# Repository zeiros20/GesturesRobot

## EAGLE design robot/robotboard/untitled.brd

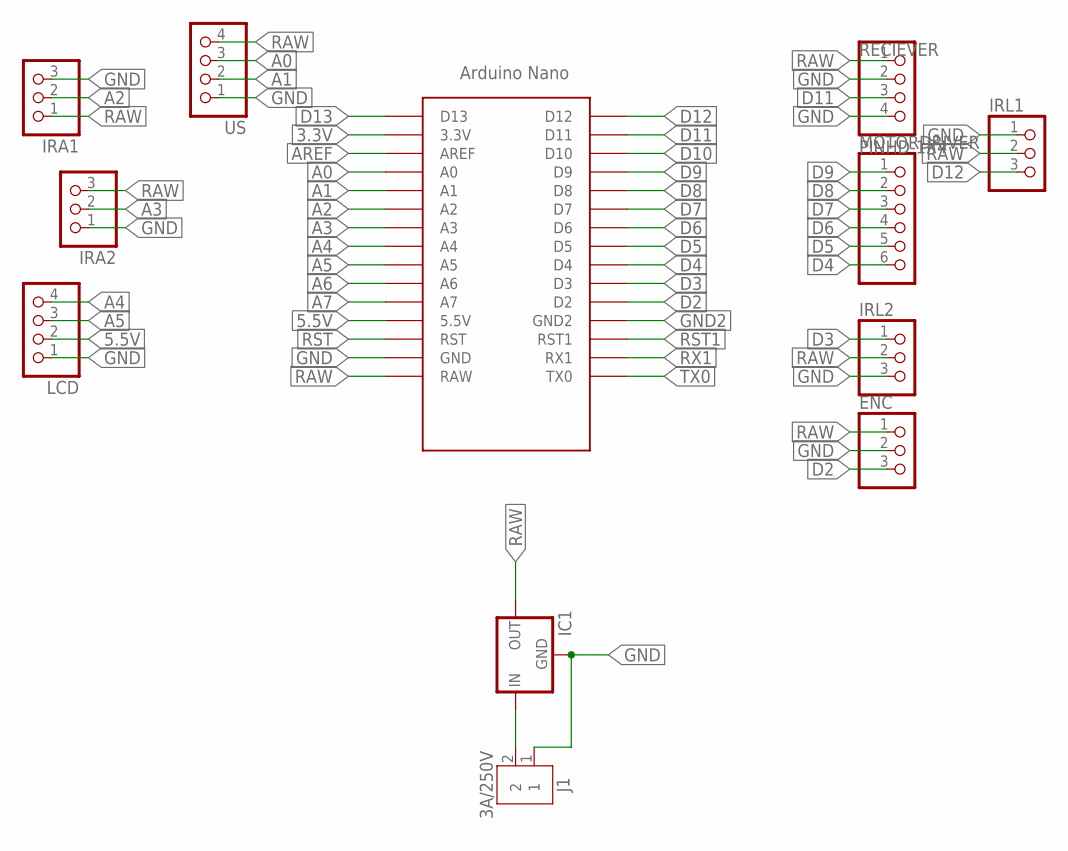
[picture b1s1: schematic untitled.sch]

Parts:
ENC: PINHD-1X3; 1X03
IC1: 78XXS
IRA1, IRA2: PINHD-1X3; 1X03
IRL1, IRL2: PINHD-1X3; 1X03
J1: 3A/250V; B2B-XH-A
LCD: PINHD-1X4; 1X04
MOTORDRIVER: PINHD-1X6; 1X06
RECIEVER: PINHD-1X4; 1X04
U$1: ARDUINO_NANO; NANO
US: PINHD-1X4; 1X04

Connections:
3.3V: U$1.3.3V
5.5V: LCD.2, U$1.5V (5.5V)
A0: U$1.A0, US.3
A1: U$1.A1, US.2
A2: IRA1.2, U$1.A2
A3: IRA2.2, U$1.A3
A4: LCD.4, U$1.A4
A5: LCD.3, U$1.A5
A6: U$1.A6
A7: U$1.A7
AREF: U$1.AREF
D2: ENC.3, U$1.D2
D3: IRL2.1, U$1.D3
D4: MOTORDRIVER.6, U$1.D4
D5: MOTORDRIVER.5, U$1.D5
D6: MOTORDRIVER.4, U$1.D6
D7: MOTORDRIVER.3, U$1.D7
D8: MOTORDRIVER.2, U$1.D8
D9: MOTORDRIVER.1, U$1.D9
D10: U$1.D10
D11: RECIEVER.3, U$1.D11
D12: IRL1.3, U$1.D12
D13: U$1.D13
GND: ENC.2, IC1.GND, IRA1.3, IRA2.1, IRL1.1, IRL2.3, J1.1, LCD.1, RECIEVER.2, RECIEVER.4, U$1.GND, US.1
GND2: U$1.GND1 (GND2)
unnamed: IC1.IN, J1.2
RAW: ENC.1, IC1.OUT, IRA1.1, IRA2.3, IRL1.2, IRL2.2, RECIEVER.1, U$1.RAW, US.4
RST: U$1.RST
RST1: U$1.RST1
RX1: U$1.RX1
TX0: U$1.TX0

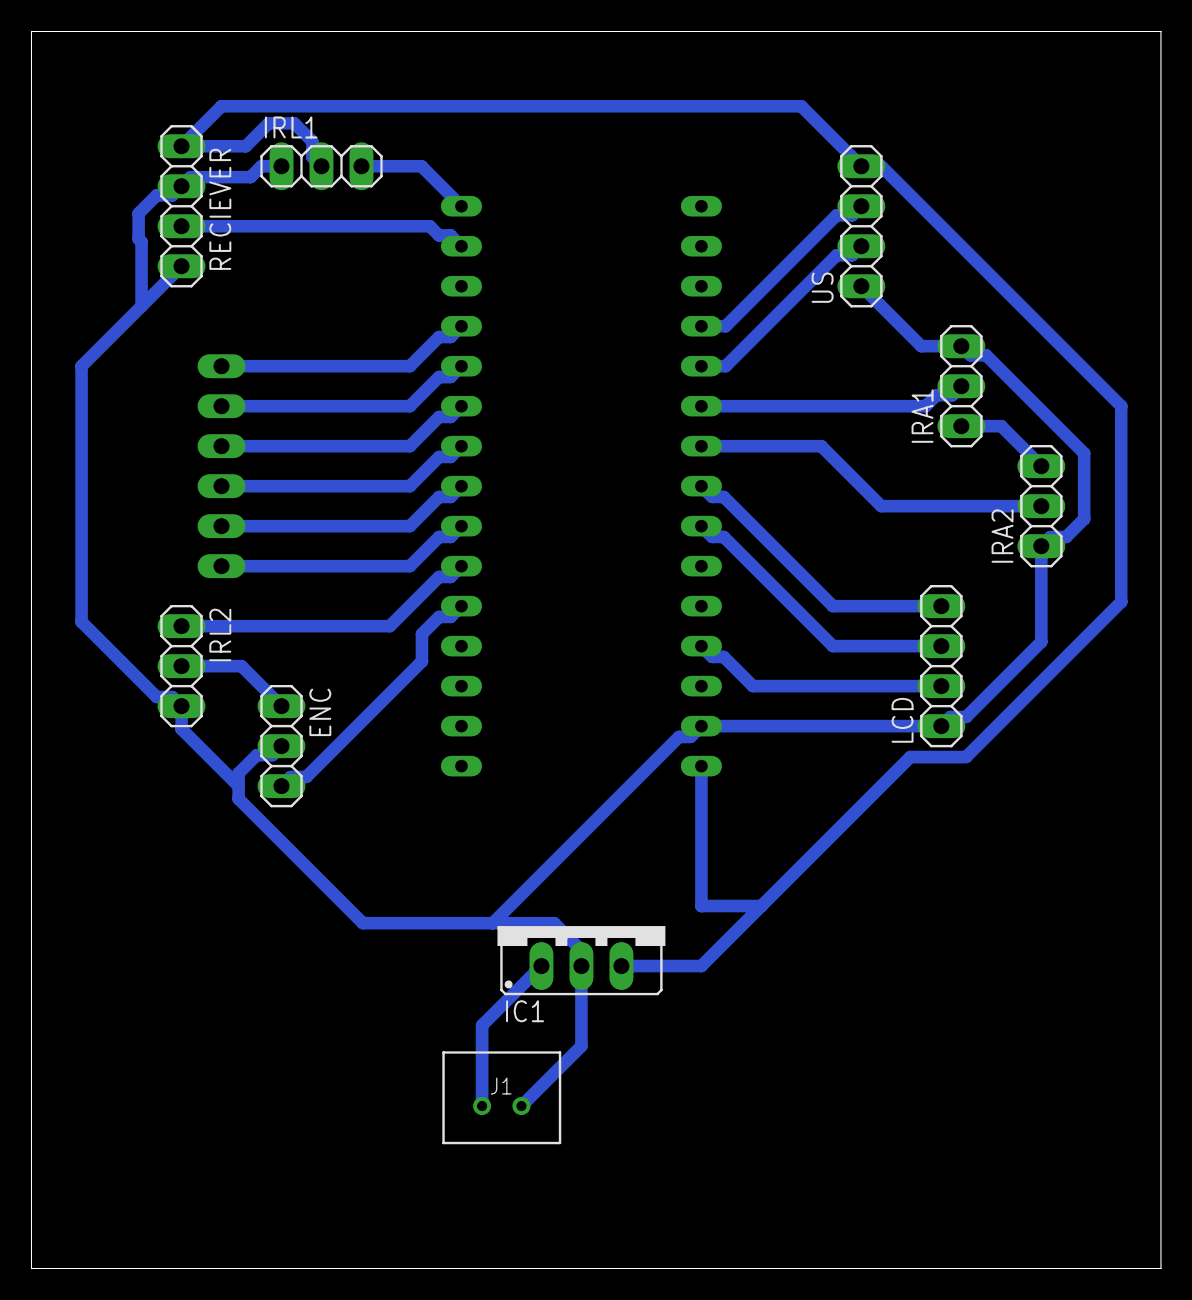
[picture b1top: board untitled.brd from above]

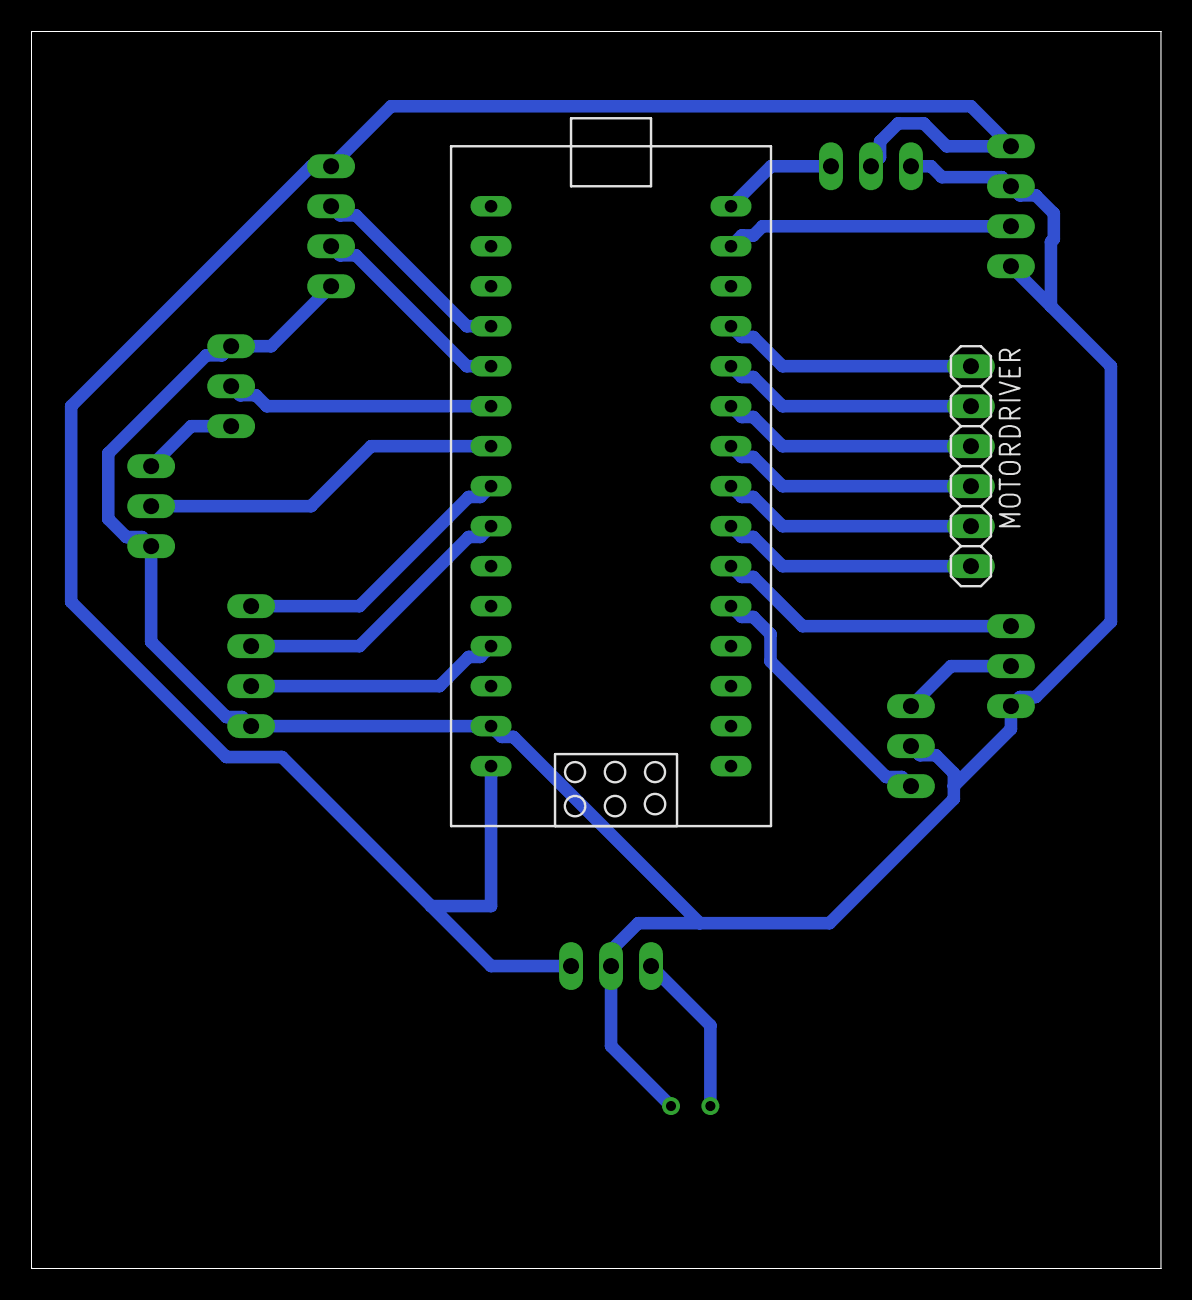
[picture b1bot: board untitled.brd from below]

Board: 2 copper layers, 71.7 x 78.6 mm, 12 parts (2 on the bottom side), 20 nets.

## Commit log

2024-04-27 added files
